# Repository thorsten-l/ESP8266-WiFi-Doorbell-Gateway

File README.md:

# ESP8266-WiFi-Doorbell-Gateway
A gateway for your doorbell button ;-)

## Screenshots
Find screenshots of the web interface in the [docs](https://github.com/thorsten-l/ESP8266-WiFi-Doorbell-Gateway/tree/master/docs) directory.

## Schematic diagrams and PCB files
Find schematic diagrams and pcb files in the [kicad](https://github.com/thorsten-l/ESP8266-WiFi-Doorbell-Gateway/tree/master/kicad) directory.

## Precompiled Firmware
Find the precompiled firmware in the [firmware](https://github.com/thorsten-l/ESP8266-WiFi-Doorbell-Gateway/tree/master/firmware) directory.

## Compile
This is a [PlatformIO](https://platformio.org/) project.

## Firmware Reset
1. Power on the WiFi Doorbell Gateway
2. Press down and hold the Power-Button during the first 5s
3. Release Power-Button when the WiFi LED starts rapidly fast blinking
4. The firmware reset ends after about 30s indicated by a permanent WiFi LED on.

## Default Settings
After a firmware reset the following values are set.

|    | value | description |
|----|-------|-------------|
| WiFi SSID | DoorbellGW-`esp id` | SSID in accesspoint mode |
| IP Address | 192.168.192.1 | ip address in accesspoint mode |
| Admin password | admin | Setup admin password |
| OTA Hostname | doorbell-gateway-1 | *O*ver *T*he *A*ir hostname |
| OTA Password | otapass | OTA firmware upload password |
| OpenHAB Callback Enabled | **false** | |
| OpenHAB Version | 1 | Callback for OpenHAB version 1 or 2 |
| OpenHAB Item Name | DoorbellGateway1 | |
| OpenHAB Host | 192.168.1.1 | |
| OpenHAB Port | 80 | |
| OpenHAB Use Authentication | false | |
| OpenHAB User | user |  |
| OpenHAB Password | password | |
| MQTT Enabled | **false** |  |
| MQTT ClientId | DoorbellGateway1 |  |
| MQTT Host | 192.168.1.1 | |
| MQTT Port | 80 | |
| MQTT Use Authentication | false | |
| MQTT User | user |  |
| MQTT Password | password | |
| MQTT Out Topic | doorbell1/out | sending callback |
| Syslog Enabled | **false** |  |
| Syslog Host | 192.168.1.1 | |
| Syslog Port (TCP) | 80 | |
| Syslog App Name | gateway-doorbell |  |

## Documentation
- Find screenshots of the web-pages [here](https://github.com/thorsten-l/ESP8266-WiFi-Doorbell-Gateway/tree/master/docs)

## Hardware
- [WEMOS D1 mini](https://wiki.wemos.cc/products:d1:d1_mini)

## References
- [PlatformIO](https://platformio.org/)
- [Arduino core for ESP8266 WiFi chip](https://github.com/esp8266/Arduino)
- [Async TCP Library for ESP8266](https://github.com/me-no-dev/ESPAsyncTCP)
- [Async Web Server for ESP8266 and ESP32](https://github.com/me-no-dev/ESPAsyncWebServer)
- [Arduino-pubsubclient - A client library for the ESP8266 that provides support for MQTT](https://github.com/heman4t/Arduino-pubsubclient)
- [Pure.CSS - A nice CSS, as GZIP it is less than 4k so it is useful for embedded devices](https://purecss.io/)

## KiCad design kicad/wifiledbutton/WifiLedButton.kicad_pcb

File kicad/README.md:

# Schematic Diagram and PCB files

## Program
These files are created with [KiCad EDA](http://kicad-pcb.org/).

## Schematic Diagrams
- [WiFi Doorbell Gateway](https://github.com/thorsten-l/ESP8266-WiFi-Doorbell-Gateway/blob/master/kicad/wifidoorbell/WifiDoorBell-D1-mini.pdf)
- [WiFi LED Button](https://github.com/thorsten-l/ESP8266-WiFi-Doorbell-Gateway/blob/master/kicad/wifiledbutton/WifiLedButton.pdf)

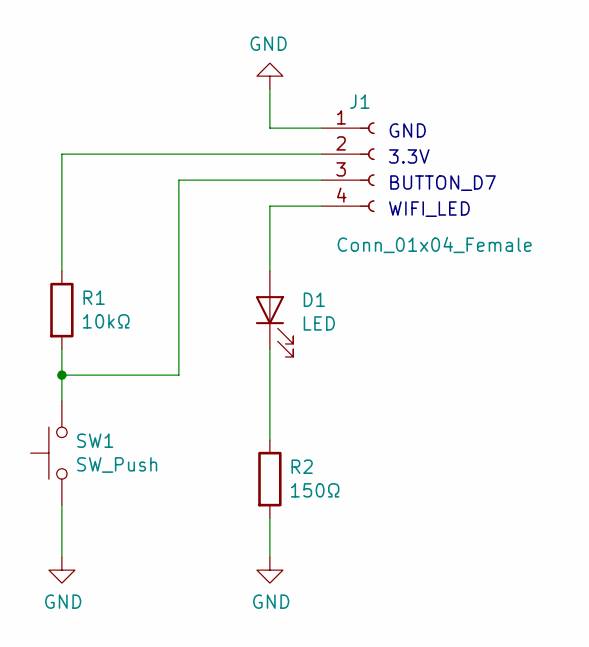
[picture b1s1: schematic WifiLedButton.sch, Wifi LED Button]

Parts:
D1: LED; LED_D5.0mm
J1: Conn_01x04_Female; TerminalBlock_TE_282834-4_1x04_P2.54mm_Horizontal
R1: 10kΩ; R_Axial_DIN0207_L6.3mm_D2.5mm_P10.16mm_Horizontal
R2: 150Ω; R_Axial_DIN0207_L6.3mm_D2.5mm_P10.16mm_Horizontal
SW1: SW_Push; SW_PUSH_6mm

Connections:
GND: J1.1, R2.2, SW1.1
unnamed: D1.1 (K), R2.1
unnamed: D1.2 (A), J1.4
unnamed: J1.2, R1.1
unnamed: J1.3, R1.2, SW1.2

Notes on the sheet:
GND
3.3V
BUTTON_D7
WIFI_LED

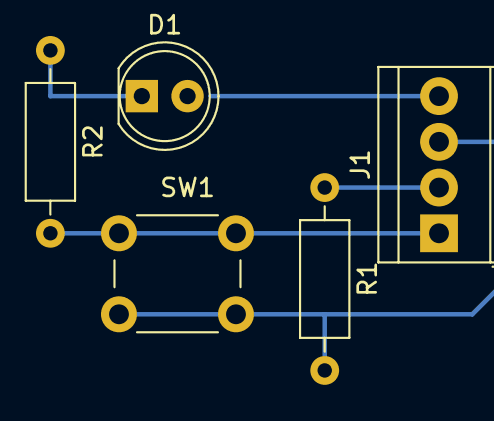
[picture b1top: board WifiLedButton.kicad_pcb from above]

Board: 2 copper layers, 5 parts (0 on the bottom side), 5 nets.

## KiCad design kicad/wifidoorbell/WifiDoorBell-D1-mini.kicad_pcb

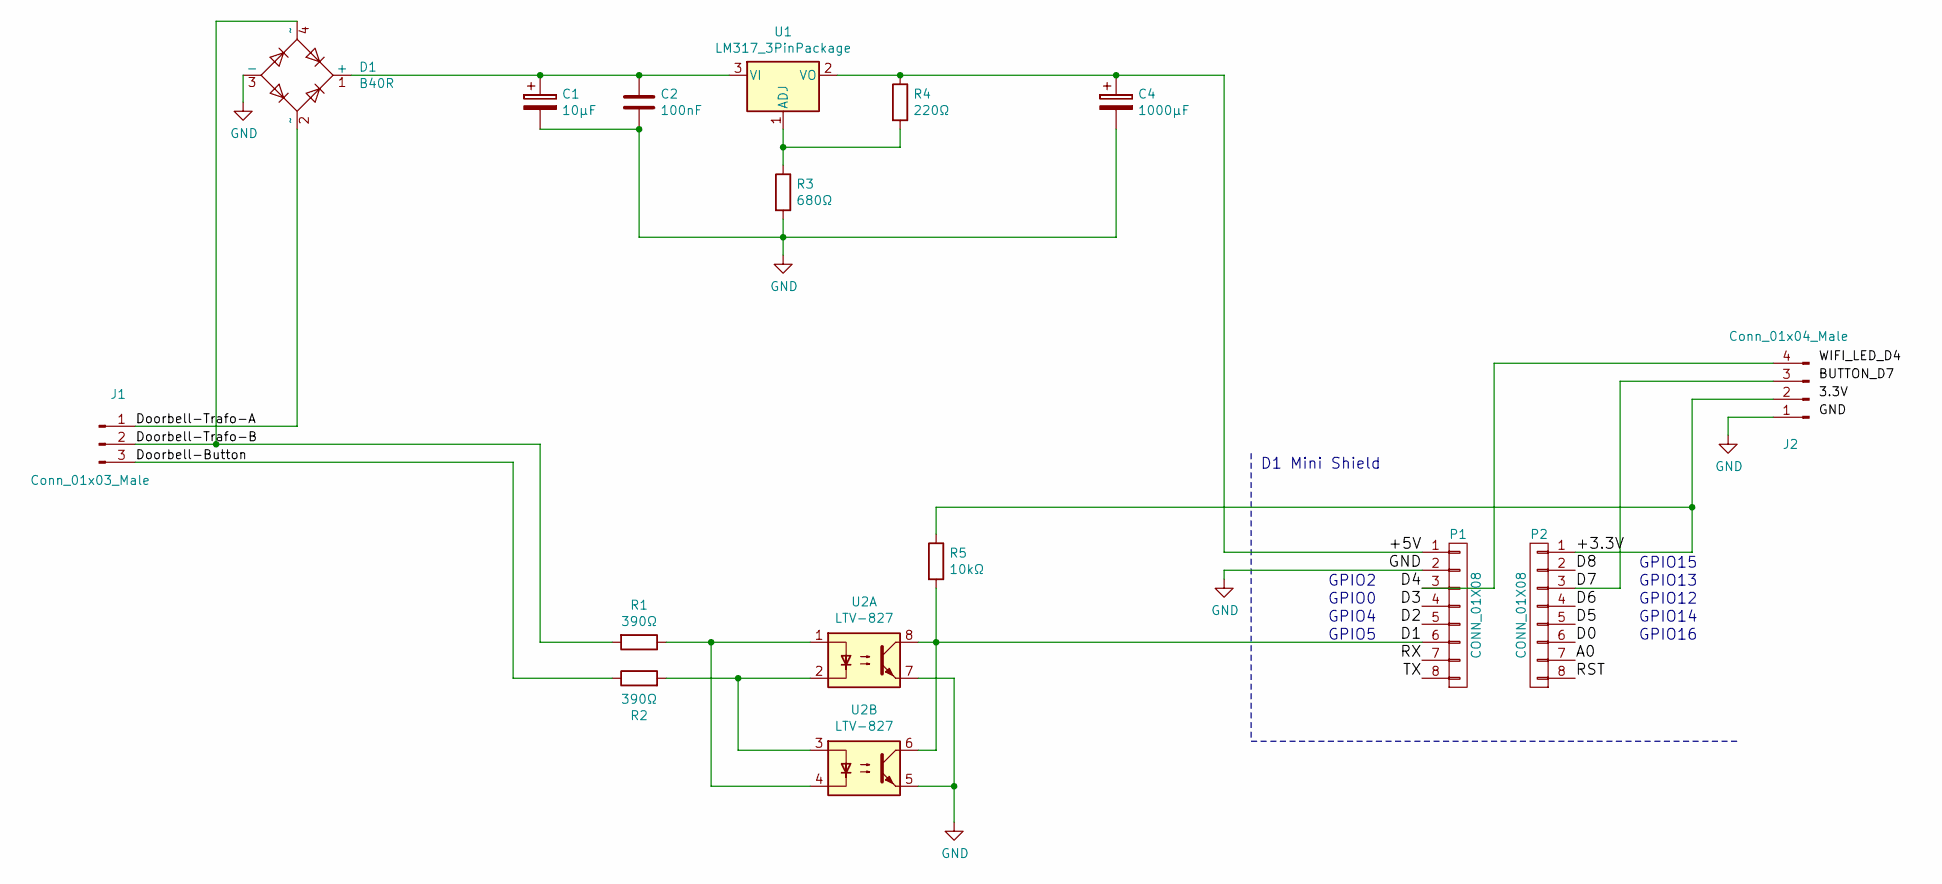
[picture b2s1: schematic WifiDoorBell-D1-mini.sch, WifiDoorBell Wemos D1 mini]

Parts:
C1: 10µF; CP_Radial_D5.0mm_P2.50mm
C2: 100nF; C_Rect_L9.0mm_W2.5mm_P7.50mm_MKT
C4: 1000µF; CP_Radial_D5.0mm_P2.50mm
D1: B40R; Diode_Bridge_Round_D9.0mm
J1: Conn_01x03_Male; TerminalBlock_TE_282834-3_1x03_P2.54mm_Horizontal
J2: Conn_01x04_Male; TerminalBlock_TE_282834-4_1x04_P2.54mm_Horizontal
P1, P2: CONN_01X08; D1_mini_Pin_Header
R1, R2: 390Ω; R_Axial_DIN0204_L3.6mm_D1.6mm_P2.54mm_Vertical
R3: 680Ω; R_Axial_DIN0204_L3.6mm_D1.6mm_P2.54mm_Vertical
R4: 220Ω; R_Axial_DIN0204_L3.6mm_D1.6mm_P2.54mm_Vertical
R5: 10kΩ; R_Axial_DIN0204_L3.6mm_D1.6mm_P2.54mm_Vertical
U1: LM317_3PinPackage; TO-220-3_Vertical
U2: LTV-827; DIP-8_W7.62mm

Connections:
/+3.3V: J2.2, P2.1, R5.1
/+5V: C4.1, P1.1, R4.1, U1.2 (VO)
/A0: P2.7
/D0: P2.6
/D1: P1.6, R5.2, U2.6, U2.8
/D2: P1.5
/D3: P1.4
/D4: J2.4, P1.3
/D5: P2.5
/D6: P2.4
/D7: J2.3, P2.3
/D8: P2.2
/Doorbell-Button: J1.3, R2.1
/Doorbell-Trafo-A: D1.2 (~~), J1.1
/Doorbell-Trafo-B: D1.4 (~~), J1.2, R1.2
/RST: P2.8
/RX: P1.7
/TX: P1.8
GND: C1.2, C2.2, C4.2, D1.3 (-), J2.1, P1.2, R3.2, U2.5, U2.7
unnamed: C1.1, C2.1, D1.1 (+), U1.3 (VI)
unnamed: R1.1, U2.1, U2.4
unnamed: R2.2, U2.2, U2.3
unnamed: R3.1, R4.2, U1.1 (ADJ)

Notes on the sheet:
GPIO2
GPIO0
GPIO4
GPIO5
GPIO15
GPIO13
GPIO12
GPIO14
GPIO16
D1 Mini Shield

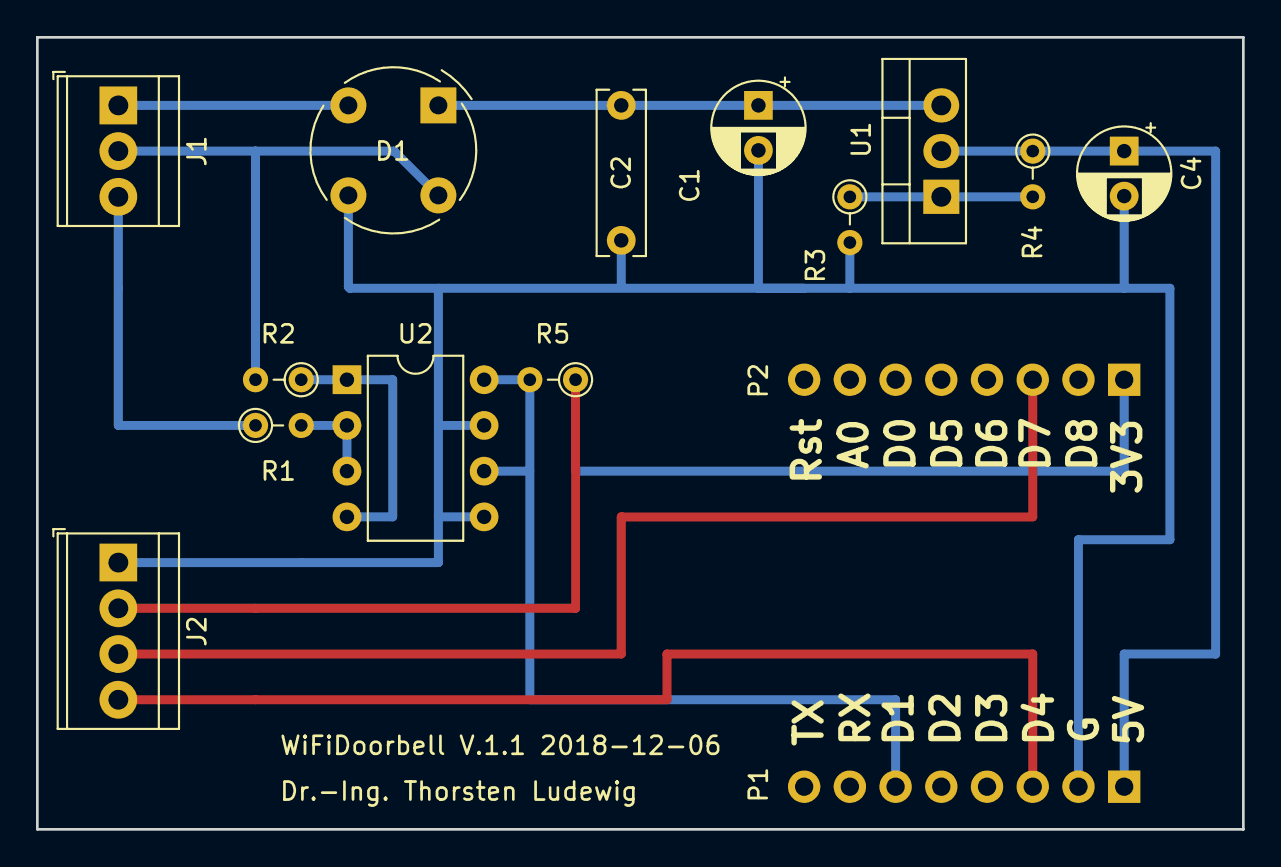
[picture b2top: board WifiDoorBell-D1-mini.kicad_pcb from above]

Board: 2 copper layers, 67.0 x 44.0 mm, 15 parts (0 on the bottom side), 13 nets.

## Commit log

2018-12-14 pcb1 files
2018-12-17 initial source text commit
2018-12-17 detailed local ip info send to syslog
2018-12-18 Handle syslog enabled flag
2018-12-18 static ip address settings added
2018-12-18 appcfgRD renamed to appcfg
2018-12-19 Wifi connected syslog info, moved from main to wifihandler
2018-12-19 release 1.0.0
2018-12-19 default settings description added
2018-12-19 Alexa settings removed
2018-12-20 documentation
2018-12-20 link to documentation added
2018-12-20 WiFi LED Button
2018-12-20 firmware directory added
2018-12-20 Precompiled firmware added
2018-12-20 settings.json should be also ignored
2018-12-20 settings.json removed
2018-12-29 private directory added
2019-01-04 use fixed library and platform versions
2019-01-04 Link to Screenshots and Schematic diagrams added
2019-01-04 new version
2019-05-26 new gitignore rules
